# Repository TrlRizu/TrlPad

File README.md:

# TrlPad

TrlPad is a 4-key macropad with a rotary encoder, an OLED display.

## Features

- 4 programmable mechanical keys (MX-style switches)
- Rotary encoder with push-button for multi-function input
- 0.91" 128x32 OLED dispvlay (SSD1306)
- Powered by Seeed Studio XIAO nRF52840 (Bluetooth + USB)
- Custom PCB

## How it evolved

### The initial concept
The design concept was to be something akin to a pedal effect. A sketch of what I thought it'd be:

### Final
Yeah, it's rather different but this is more feasible and it's simple yet punk-y.

### PCB
Below is the schematic:

Below is the PCB routing:

---

## Bill of Materials (BOM)

| #  | Reference       | Value                | Footprint                                         | Qty | Link                                                                 | Price (USD) | Running Price (USD) |
|----|----------------|--------------------|--------------------------------------------------|-----|----------------------------------------------------------------------|-------------|-------------------|
| 1  | D1, D2, D3, D4 | D                  | Diode_THT:D_DO-35_SOD27_P7.62mm_Horizontal     | 4   | [AliExpress](https://www.aliexpress.com/item/1005007625866819.html?spm=a2g0o.productlist.main.1.7aeadCCUdCCUEm&aem_p4p_detail=2025102119550212594792942763680001106495&algo_pvid=a434d49d-5a77-4968-bc6d-58301a94e042&pdp_ext_f=%7B%22order%22%3A%2241%22%2C%22eval%22%3A%221%22%2C%22fromPage%22%3A%22search%22%7D&utparam-url=scene%3Asearch%7Cquery_from%3A%7Cx_object_id%3A1005007625866819%7C_p_origin_prod%3A&search_p4p_id=2025102119550212594792942763680001106495_1) | 1.41        | 1.41              |
| 2  | D5             | 1N4148W            | Diode_SMD:D_SOD-123                              | 1   | [AliExpress](https://www.aliexpress.com/item/1005007160279747.html?spm=a2g0o.productlist.main.1.4bea610605GMvi&algo_pvid=69e8bef0-e1cb-4e4b-bf00-d1d1762fa9c0&pdp_ext_f=%7B%22order%22%3A%2254%22%2C%22eval%22%3A%221%22%2C%22fromPage%22%3A%22search%22%7D&utparam-url=scene%3Asearch%7Cquery_from%3A%7Cx_object_id%3A1005007160279747%7C_p_origin_prod%3A#nav-description) | 1.95        | 3.36              |
| 3  | R1             | 806k               | Resistor_SMD:R_0805_2012Metric                  | 1   | [AliExpress](https://www.aliexpress.com/item/1005008964311488.html?spm=a2g0o.productlist.main.1.7afa2680Uz7Hdj&algo_pvid=6147d466-e002-4eeb-800f-490fd843ce71&pdp_ext_f=%7B%22order%22%3A%22-1%22%2C%22eval%22%3A%221%22%2C%22fromPage%22%3A%22search%22%7D&utparam-url=scene%3Asearch%7Cquery_from%3A%7Cx_object_id%3A1005008964311488%7C_p_origin_prod%3A) | 0.66        | 4.50              |
| 4  | R2             | 2M                 | Resistor_SMD:R_0805_2012Metric                  | 1   | [AliExpress](https://www.aliexpress.com/item/1005008964311488.html?spm=a2g0o.productlist.main.1.7afa2680Uz7Hdj&algo_pvid=6147d466-e002-4eeb-800f-490fd843ce71&pdp_ext_f=%7B%22order%22%3A%22-1%22%2C%22eval%22%3A%221%22%2C%22fromPage%22%3A%22search%22%7D&utparam-url=scene%3Asearch%7Cquery_from%3A%7Cx_object_id%3A1005008964311488%7C_p_origin_prod%3A) | 0.48        | 4.50              |
| 5  | SW1, SW2, SW3, SW4 | SW_Push         | Button_Switch_Keyboard:SW_Cherry_MX_1.00u_PCB  | 4   | [AliExpress](https://www.aliexpress.com/item/1005006255961111.html?spm=a2g0o.productlist.main.21.1a957561CIH3R9&algo_pvid=cce3f2b7-a65c-4480-a261-c810498f6d66&pdp_ext_f=%7B%22order%22%3A%22880%22%2C%22eval%22%3A%221%22%2C%22fromPage%22%3A%22search%22%7D&utparam-url=scene%3Asearch%7Cquery_from%3A%7Cx_object_id%3A1005006255961111%7C_p_origin_prod%3A#nav-specification) | 1.01        | 5.51              |
| 6  | SW5             | RotaryEncoder_Switch | Rotary_Encoder:RotaryEncoder_Alps_EC11E-Switch_Vertical_H20mm | 1 | [AliExpress](https://www.aliexpress.com/item/1005006693443387.html?spm=a2g0o.productlist.main.3.3a0754e8XWgMGL&aem_p4p_detail=2025102123460313199915294252100001307677&algo_pvid=41fcd1eb-5860-43c2-b696-f7e4df5bee48&pdp_ext_f=%7B%22order%22%3A%2268%22%2C%22eval%22%3A%221%22%2C%22fromPage%22%3A%22search%22%7D&utparam-url=scene%3Asearch%7Cquery_from%3A%7Cx_object_id%3A1005006693443387%7C_p_origin_prod%3A&search_p4p_id=2025102123460313199915294252100001307677_3) | 0.63        | 6.14              |
| 7  | TP1, TP2        | TestPoint          | TestPoint:TestPoint_Pad_D2.0mm                  | 2   | —                                                                    | —           | 6.14              |
| 8  | U1             | XIAO-nRF52840-SMD  | Modified:modified-XIAO-nRF52840-SMD             | 1   | [AliExpress](https://www.aliexpress.com/item/1005006988954136.html?spm=a2g0o.productlist.main.3.45da24c867QaLR&algo_pvid=7bc7b30e-e03b-4713-8945-3bacfdca3c01&pdp_ext_f=%7B%22order%22%3A%22454%22%2C%22eval%22%3A%221%22%2C%22fromPage%22%3A%22search%22%7D&utparam-url=scene%3Asearch%7Cquery_from%3A%7Cx_object_id%3A1005006988954136%7C_p_origin_prod%3A) | 10.11       | 16.25             |
| 9  | U2             | 128x32_OLED_S      | zzz_Project:SSD1306-0.91-OLED-4pin-128x32       | 1   | [AliExpress](https://www.aliexpress.com/item/1005008640132638.html?spm=a2g0o.productlist.main.2.7a63IqANIqANd9&algo_pvid=2b485676-1627-4ff0-95f6-07098624fd68&pdp_ext_f=%7B%22order%22%3A%221992%22%2C%22eval%22%3A%221%22%2C%22fromPage%22%3A%22search%22%7D&utparam-url=scene%3Asearch%7Cquery_from%3A%7Cx_object_id%3A1005008640132638%7C_p_origin_prod%3A) | 2.24        | 18.49             |
| 10 | Shipping costs  | —                  | for AliExpress check cart.png                    | —   | —                                                                    | 3.05        | 21.54             |
| 11 | 3D Printed case | —                  | check screenshot 3dCase_bill.png                 | —   | [3Ding](https://print.3ding.in/upload)                               | 16.29       | 37.83             |
| 12 | PCB            | —                  | from JLPCB, check screenshot jlcpcb.png          | —   | —                                                                    | 7.56        | 45.39             |

**Total Estimated Cost:** 45.39 USD

####  Note: I am trying to get the case 3D printed using #printing-legion, or if that doesn't work out, I'll cover the cost on my own!
---

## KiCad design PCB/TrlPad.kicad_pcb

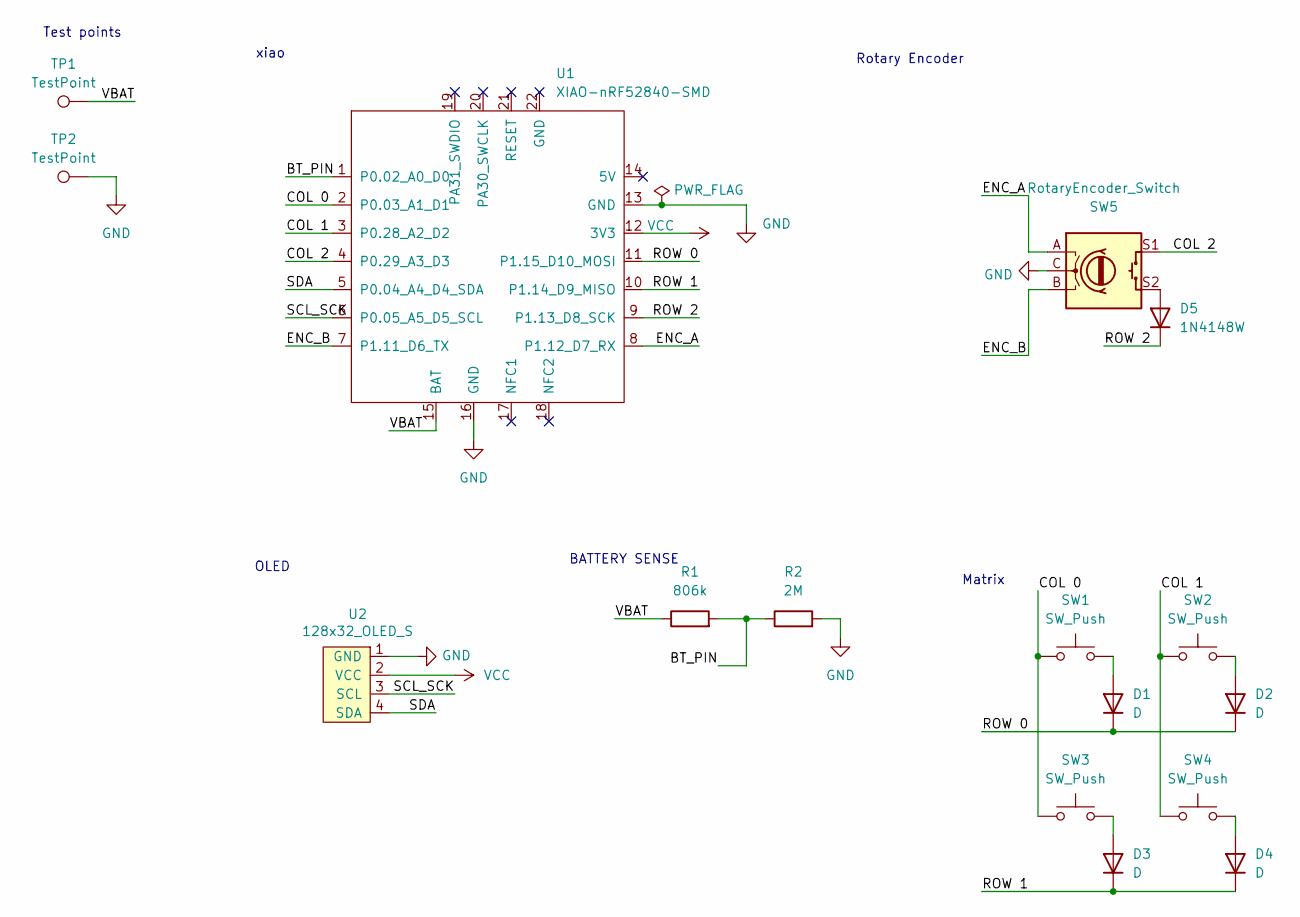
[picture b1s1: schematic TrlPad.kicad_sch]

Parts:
D1, D2, D3, D4: D; D_DO-35_SOD27_P7.62mm_Horizontal
D5: 1N4148W; D_SOD-123
R1: 806k; R_0805_2012Metric
R2: 2M; R_0805_2012Metric
SW1, SW2, SW3, SW4: SW_Push; SW_Cherry_MX_1.00u_PCB
SW5: RotaryEncoder_Switch; RotaryEncoder_Alps_EC11E-Switch_Vertical_H20mm
TP1, TP2: TestPoint; TestPoint_Pad_D2.0mm
U1: XIAO-nRF52840-SMD; modified-XIAO-nRF52840-SMD
U2: 128x32_OLED_S; SSD1306-0.91-OLED-4pin-128x32

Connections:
/BT_PIN: R1.2, R2.1, U1.1 (P0.02_A0_D0)
/COL 0: SW1.1, SW3.1, U1.2 (P0.03_A1_D1)
/COL 1: SW2.1, SW4.1, U1.3 (P0.28_A2_D2)
/COL 2: SW5.S1, U1.4 (P0.29_A3_D3)
/ENC_A: SW5.A, U1.8 (P1.12_D7_RX)
/ENC_B: SW5.B, U1.7 (P1.11_D6_TX)
/ROW 0: D1.1 (K), D2.1 (K), U1.11 (P1.15_D10_MOSI)
/ROW 1: D3.1 (K), D4.1 (K), U1.10 (P1.14_D9_MISO)
/ROW 2: D5.1 (K), U1.9 (P1.13_D8_SCK)
/SCL_SCK: U1.6 (P0.05_A5_D5_SCL), U2.3 (SCL)
/SDA: U1.5 (P0.04_A4_D4_SDA), U2.4 (SDA)
/VBAT: R1.1, TP1.1, U1.15 (BAT)
GND: R2.2, SW5.C, TP2.1, U1.13 (GND), U1.16 (GND), U2.1 (GND)
unnamed: D1.2 (A), SW1.2
unnamed: D2.2 (A), SW2.2
unnamed: D3.2 (A), SW3.2
unnamed: D4.2 (A), SW4.2
unnamed: D5.2 (A), SW5.S2
VCC: U1.12 (3V3), U2.2 (VCC)

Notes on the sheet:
OLED
Rotary Encoder
Test points
BATTERY SENSE
Matrix
xiao

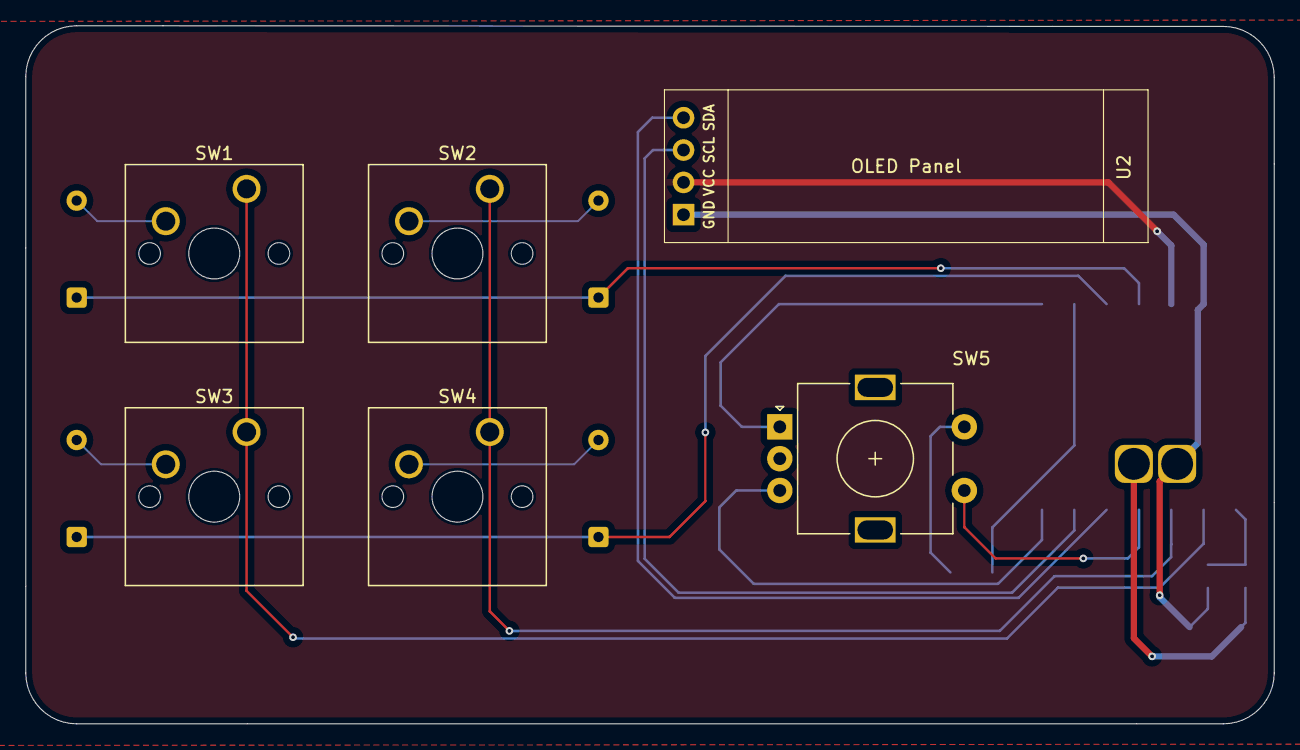
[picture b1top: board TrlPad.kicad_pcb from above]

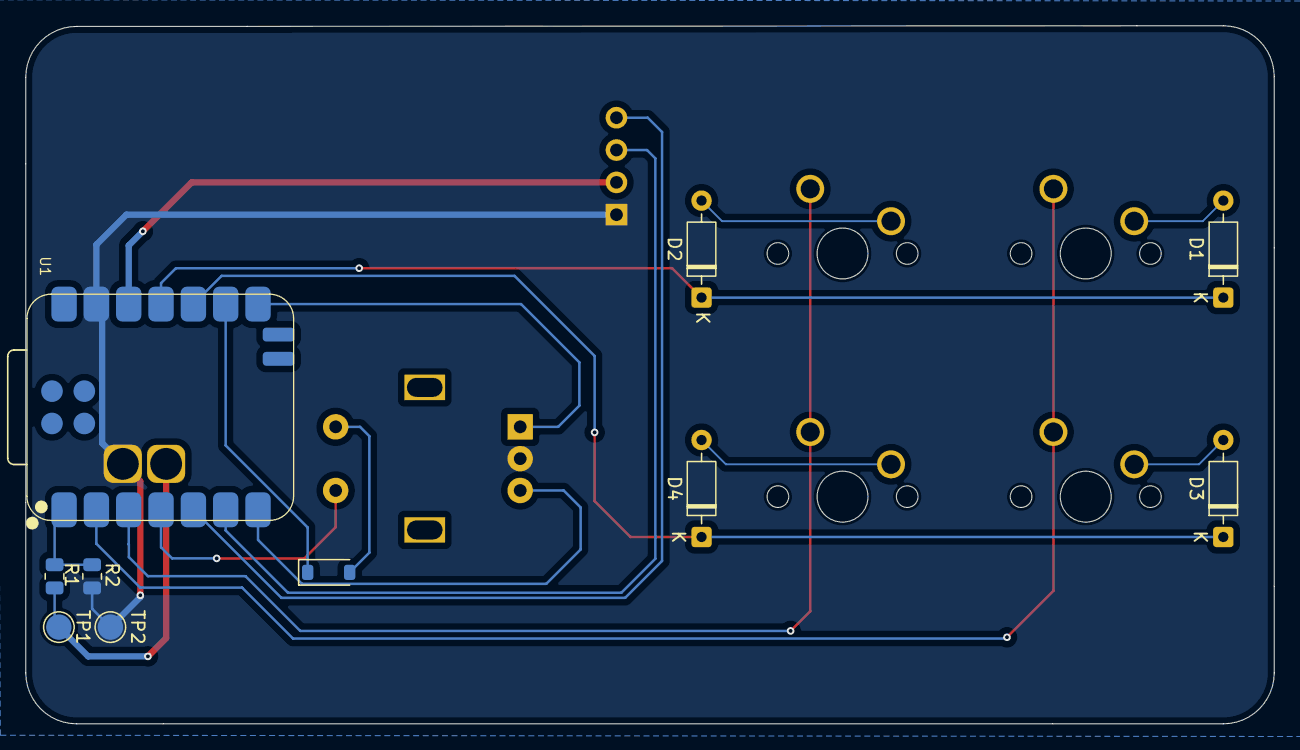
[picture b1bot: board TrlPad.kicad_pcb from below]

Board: 2 copper layers, 98.1 x 54.8 mm, 16 parts (10 on the bottom side), 19 nets.

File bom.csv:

#,Reference,Value,Footprint,Qty,Link,Price,Running Price
1,"D1,D2,D3,D4",D,Diode_THT:D_DO-35_SOD27_P7.62mm_Horizontal,4,https://www.aliexpress.com/item/1005007625866819.html?spm=a2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,1.41,1.41
2,D5,1N4148W,Diode_SMD:D_SOD-123,1,https://www.aliexpress.com/item/1005007160279747.html?spm=a2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,1.95,3.36
3,R1,806k,Resistor_SMD:R_0805_2012Metric,1,https://www.aliexpress.com/item/1005008964311488.html?spm=a2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,0.66,4.5
4,R2,2M,Resistor_SMD:R_0805_2012Metric,1,https://www.aliexpress.com/item/1005008964311488.html?spm=a2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,0.48,4.5
5,"SW1,SW2,SW3,SW4",SW_Push,Button_Switch_Keyboard:SW_Cherry_MX_1.00u_PCB,4,https://www.aliexpress.com/item/1005006255961111.html?spm=a2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,1.01,5.51
6,SW5,RotaryEncoder_Switch,Rotary_Encoder:RotaryEncoder_Alps_EC11E-Switch_Vertical_H20mm,1,https://www.aliexpress.com/item/1005006693443387.html?spm=a2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,0.63,6.14
7,"TP1,TP2",TestPoint,TestPoint:TestPoint_Pad_D2.0mm,2,,,
8,U1,XIAO-nRF52840-SMD,Modified:modified-XIAO-nRF52840-SMD,1,https://www.aliexpress.com/item/1005006988954136.html?spm=a2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,10.11,16.25
9,U2,128x32_OLED_S,zzz_Project:SSD1306-0.91-OLED-4pin-128x32,1,https://www.aliexpress.com/item/1005008640132638.html?spm=a2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,2.24,18.49
10,Shipping costs ,,for AliExpress check cart.png,,,3.05,21.54
11,3D Printed case,,check screenshot 3dCase_bill.png,,https://print.3ding.in/upload,16.29,37.83
12,PCB,,"from JLPCB, check screenshot jlcpcb.png",,,7.56,45.39
,Total,,,,,,45.39

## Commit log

2025-10-21 v0.1
2025-10-21 renamed bom
2025-10-23 Updated repo
2025-10-23 README.md update
2025-10-23 Updated BOM
2025-10-24 Updated BOM + fixed PCB
